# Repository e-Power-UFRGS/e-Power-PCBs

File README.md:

# e-Power-PCBs

## Index

#### e-Power_conventions: Standard conventions for all PCBs
The image shows an example with conventions regarding the description data of the PCBs. One way to implemment this conventions is oppening 2 KiCad Pcbnew windows, one with the file you want to update and other with the e-Power_conventions.kicad_pcb and the copy the standard from one window to the other (yes, this is possible on the current versions of KiCad!).

#### BMS_20S: Battery Management System with 20S measurement capability

#### TSAL: Tractive System Alternating Lights 

## License
[MIT](https://choosealicense.com/licenses/mit/)

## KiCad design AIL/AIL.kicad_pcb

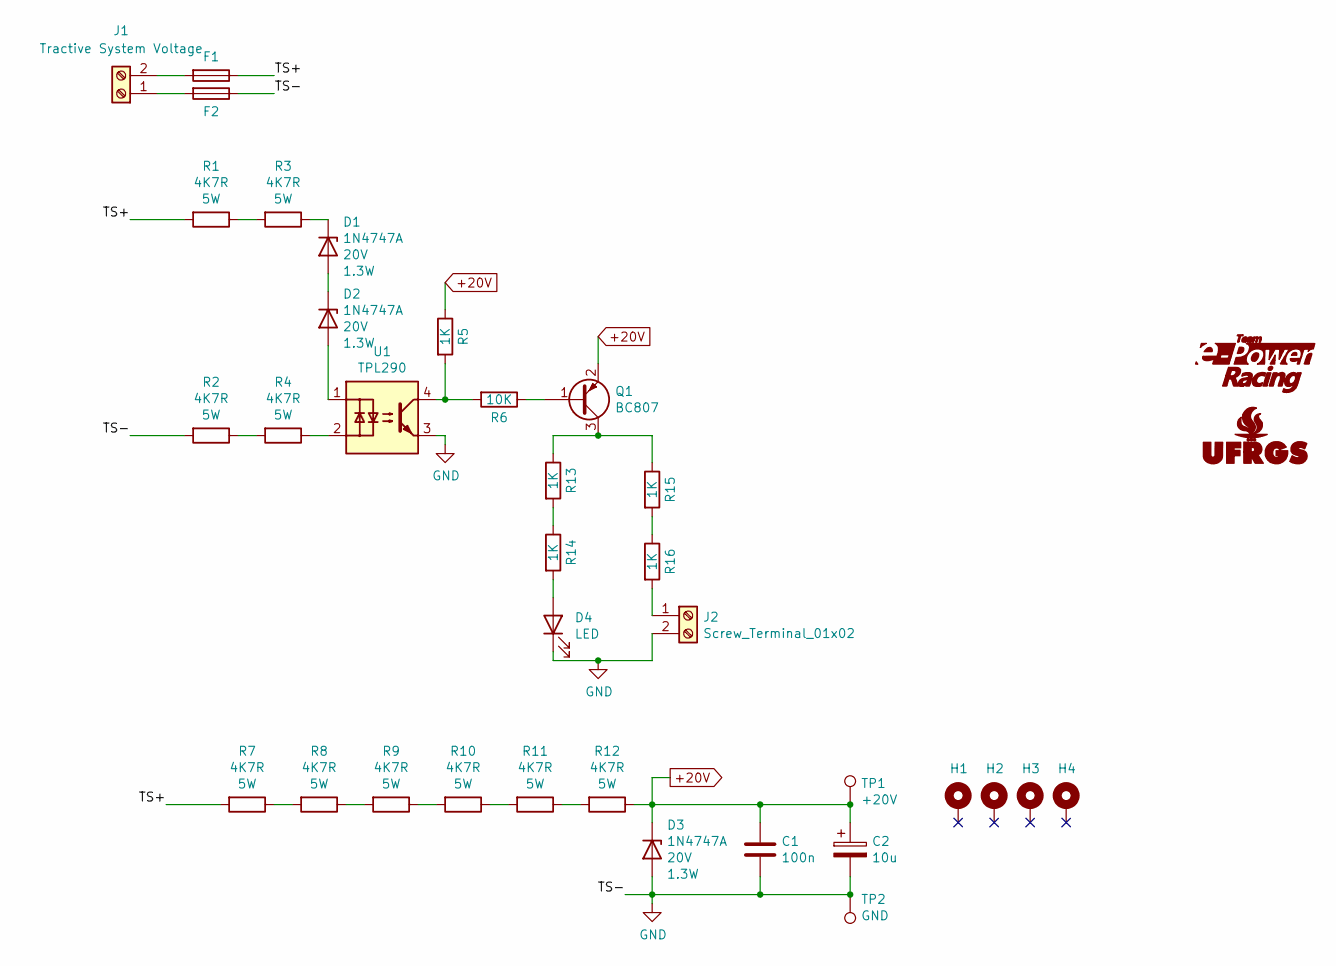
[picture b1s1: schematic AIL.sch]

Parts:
C1: 100n; C_0805_2012Metric
C2: 10u; CP_Elec_8x10
D1, D2, D3: 1N4747A; DO-35_SMD; Voltage 20V
D4: LED; LED_0805_1.15x1.40mm_HandSolder
F1, F2: Fuse_1206; FUSE_1206_3216Metric
G1: Logo_e-Power_Large; Logo_e-Power_16.5x8.0mm_SilkS
G2: Logo_UFRGS_Large; Logo_UFRGS_14.7x8.0mm_SilkS
H1, H2, H3, H4: NC; MountingHole_3.2mm_M3_Pad_Via
J1, J2: Screw_Terminal_01x02; TerminalBlock_Phoenix_MKDS-1,5-2_1x02_P5.08mm_Horizontal
Q1: BC807; SOT-23
R1, R2, R3, R4, R7, R8, R9, R10, R11, R12: 4K7R; R_Axial_DIN0617_L17.0mm_D6.0mm_P25.40mm_Horizontal
R5, R13, R14, R15, R16: 1K; R_0805_2012Metric_Pad1.15x1.40mm_HandSolder
R6: 10K; R_0805_2012Metric_Pad1.15x1.40mm_HandSolder
TP1: +20V; TestPoint_Pad_D1.0mm
TP2: GND; TestPoint_Pad_D1.0mm
U1: TPL290; DIP-4_W10.16mm

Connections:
+20V: C1.1, C2.1, D3.1 (K), Q1.2 (E), R5.1, R12.1, TP1.1
/TS+: F1.1, R1.2, R7.2
GND: C1.2, C2.2, D3.2 (A), D4.1 (K), F2.1, J2.2, R2.2, TP2.1, U1.3
unnamed: D1.1 (K), R3.1
unnamed: D1.2 (A), D2.1 (K)
unnamed: D2.2 (A), U1.1
unnamed: D4.2 (A), R14.2
unnamed: F1.2, J1.2
unnamed: F2.2, J1.1
unnamed: J2.1, R16.2
unnamed: Q1.1 (B), R6.1
unnamed: Q1.3 (C), R13.1, R15.1
unnamed: R1.1, R3.2
unnamed: R2.1, R4.2
unnamed: R4.1, U1.2
unnamed: R5.2, R6.2, U1.4
unnamed: R7.1, R8.2
unnamed: R8.1, R9.2
unnamed: R10.1, R11.2
unnamed: R9.1, R10.2
unnamed: R11.1, R12.2
unnamed: R13.2, R14.1
unnamed: R15.2, R16.1

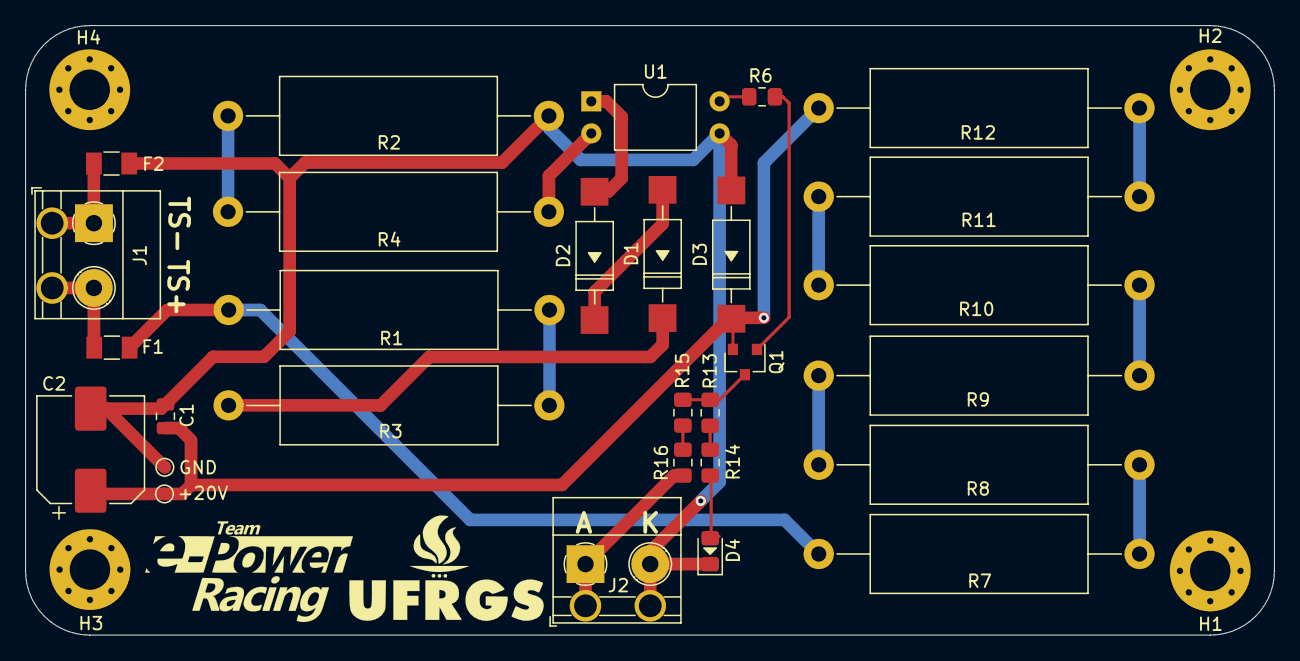
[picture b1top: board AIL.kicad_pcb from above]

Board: 2 copper layers, 98.9 x 48.3 mm, 35 parts (0 on the bottom side), 23 nets.

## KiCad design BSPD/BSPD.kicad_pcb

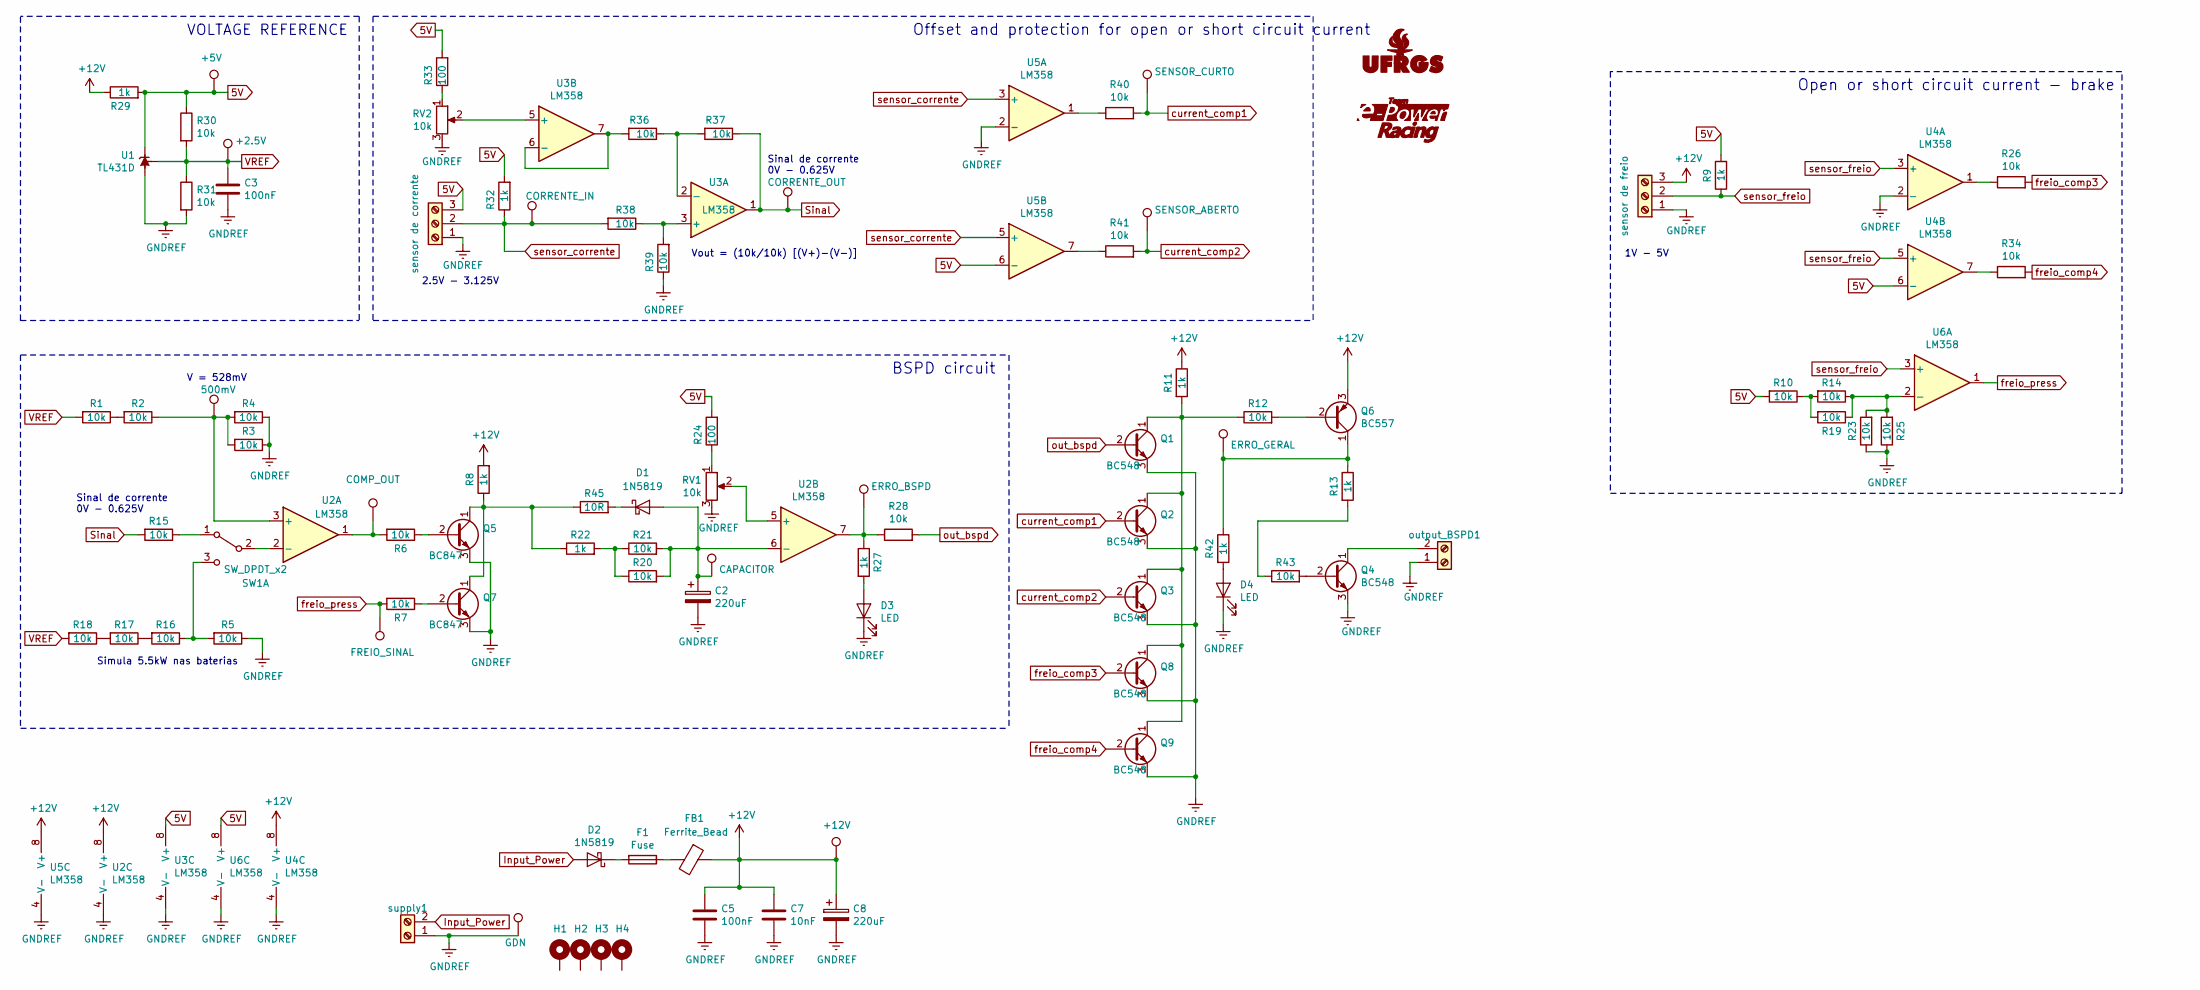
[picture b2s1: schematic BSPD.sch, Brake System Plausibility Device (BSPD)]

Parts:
C2, C8: 220uF; CP_Elec_10x10
C3, C5: 100nF; C_0805_2012Metric
C7: 10nF; C_0805_2012Metric
D1, D2: 1N5819; DO-214AC
D3, D4: LED; LED_0805_1.15x1.40mm_HandSolder
F1: Fuse; Fuse_0805_2012Metric
FB1: Ferrite_Bead; FB_0603_1608Metric
G1: Logo_UFRGS_Large; Logo_UFRGS_14.7x8.0mm_SilkS
G2: Logo_e-Power_Large; Logo_e-Power_16.5x8.0mm_SilkS
H1, H2, H3, H4: MountingHole_Pad; MountingHole_3.2mm_M3_Pad_Via
J1: sensor de corrente; TerminalBlock_Phoenix_MKDS-1,5-3_1x03_P5.00mm_Horizontal
Q1, Q2, Q3, Q4, Q8, Q9: BC548; SOT-23
Q5, Q7: BC847; SOT-23
Q6: BC557; SOT-23
R1, R2, R3, R4, R5, R6, R7, R10, R12, R14, R15, R16, R17, R18, R19, R20, R21, R23, R25, R26, R28, R30, R31, R34, R36, R37, R38, R39, R40, R41, R43: 10k; R_0805_2012Metric
R8, R9, R11, R13, R22, R27, R29, R32, R42: 1k; R_0805_2012Metric
R24, R33: 100; R_0805_2012Metric
R45: 10R; R_0805_2012Metric
RV1, RV2: 10k; Potentiometer_Bourns_3266Y_Vertical
SW1: SW_DPDT_x2; PinHeader_1x03_P2.54mm_Vertical
TP1: +5V; TestPoint_Pad_D1.0mm
TP2: 500mV; TestPoint_Pad_D1.0mm
TP3: +2.5V; TestPoint_Pad_D1.0mm
TP4: GDN; TestPoint_Pad_D1.0mm
TP5: CORRENTE_IN; TestPoint_Pad_D1.0mm
TP6: CORRENTE_OUT; TestPoint_Pad_D1.0mm
TP7: +12V; TestPoint_Pad_D1.0mm
TP8: COMP_OUT; TestPoint_Pad_D1.0mm
TP9: FREIO_SINAL; TestPoint_Pad_D1.0mm
TP10: CAPACITOR; TestPoint_Pad_D1.0mm
TP11: ERRO_BSPD; TestPoint_Pad_D1.0mm
TP12: SENSOR_CURTO; TestPoint_Pad_D1.0mm
TP13: SENSOR_ABERTO; TestPoint_Pad_D1.0mm
TP14: ERRO_GERAL; TestPoint_Pad_D1.0mm
U1: TL431D; SOT-23
U2, U3, U4, U5, U6: LM358; SOIC-8_3.9x4.9mm_P1.27mm
output_BSPD1: Screw_Terminal_01x02; TerminalBlock_Phoenix_MKDS-1,5-2_1x02_P5.08mm_Horizontal
sensor_freio1: sensor de freio; TerminalBlock_Phoenix_MKDS-1,5-3_1x03_P5.00mm_Horizontal
supply1: Screw_Terminal_01x02; TerminalBlock_Phoenix_MKDS-1,5-2_1x02_P5.08mm_Horizontal

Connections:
5V: J1.3, R9.2, R10.2, R24.2, R29.2, R30.1, R32.2, R33.2, TP1.1, U1.1 (K), U3.8 (V+), U4.6 (-), U5.6 (-), U6.8 (V+)
+12V: C5.1, C7.1, C8.1, FB1.1, Q6.3 (E), R8.2, R11.1, R29.1, TP7.1, U2.8 (V+), U4.8 (V+), U5.8 (V+), sensor_freio1.3; also elsewhere on the board
Input_Power: D2.2 (A), supply1.2; also elsewhere on the board
unnamed: C2.1, D1.2 (A), R20.2, R21.2, TP10.1, U2.6 (-)
unnamed: D1.1 (K), R45.2
unnamed: D2.1 (K), F1.2
unnamed: D3.2 (A), R27.2
unnamed: D4.2 (A), R42.2
unnamed: F1.1, FB1.2
unnamed: Q1.1 (C), Q2.1 (C), Q3.1 (C), Q8.1 (C), Q9.1 (C), R11.2, R12.1
unnamed 14: Q4.1 (C), output_BSPD1.2; also elsewhere on the board
unnamed: Q4.2 (B), R43.2
unnamed: Q5.1 (C), Q7.1 (C), R8.1, R22.1, R45.1
unnamed: Q5.2 (B), R6.1
unnamed: Q6.1 (C), R13.1, R42.1, TP14.1
unnamed: Q6.2 (B), R12.2
unnamed: Q7.2 (B), R7.1
unnamed: R1.1, R2.2
unnamed: R2.1, R3.2, R4.2, TP2.1, U2.3 (+)
unnamed: R6.2, TP8.1, U2.1
unnamed: R10.1, R14.2, R19.2
unnamed: R13.2, R43.1
unnamed: R14.1, R19.1, R23.2, R25.2, U6.2 (-)
unnamed: R15.1, SW1.1 (A)
unnamed: R5.2, R16.1, SW1.3 (C)
unnamed: R16.2, R17.1
unnamed: R17.2, R18.1
unnamed: R20.1, R21.1, R22.2
unnamed: R24.1, RV1.1
unnamed: R26.1, U4.1
unnamed: R27.1, R28.1, TP11.1, U2.7
unnamed: R33.1, RV2.1
unnamed: R34.1, U4.7
unnamed: R36.1, R37.2, U3.2 (-)
unnamed: R36.2, U3.6 (-), U3.7
unnamed: R38.1, R39.2, U3.3 (+)
unnamed: R40.1, U5.1
unnamed: R41.1, U5.7
unnamed: RV1.2, U2.5 (+)
unnamed: RV2.2, U3.5 (+)
unnamed: SW1.2 (B), U2.2 (-)
Sinal: R15.2, R37.1, TP6.1, U3.1
current_comp1: Q2.2 (B), R40.2, TP12.1
current_comp2: Q3.2 (B), R41.2, TP13.1
freio_comp3: Q8.2 (B), R26.2
freio_comp4: Q9.2 (B), R34.2
freio_press: R7.2, TP9.1, U6.1
out_bspd: Q1.2 (B), R28.2
sensor_corrente: J1.2, R32.1, R38.2, TP5.1, U5.3 (+), U5.5 (+)
sensor_freio: R9.1, U4.3 (+), U4.5 (+), U6.3 (+), sensor_freio1.2; also elsewhere on the board

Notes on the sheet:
VOLTAGE REFERENCE
Offset and protection for open or short circuit current
BSPD circuit
Vout = (10k/10k) [(V+)-(V-)]
Simula 5.5kW nas baterias
V = 528mV
2.5V - 3.125V
Sinal de corrente 0V - 0.625V
1V - 5V
Open or short circuit current - brake

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
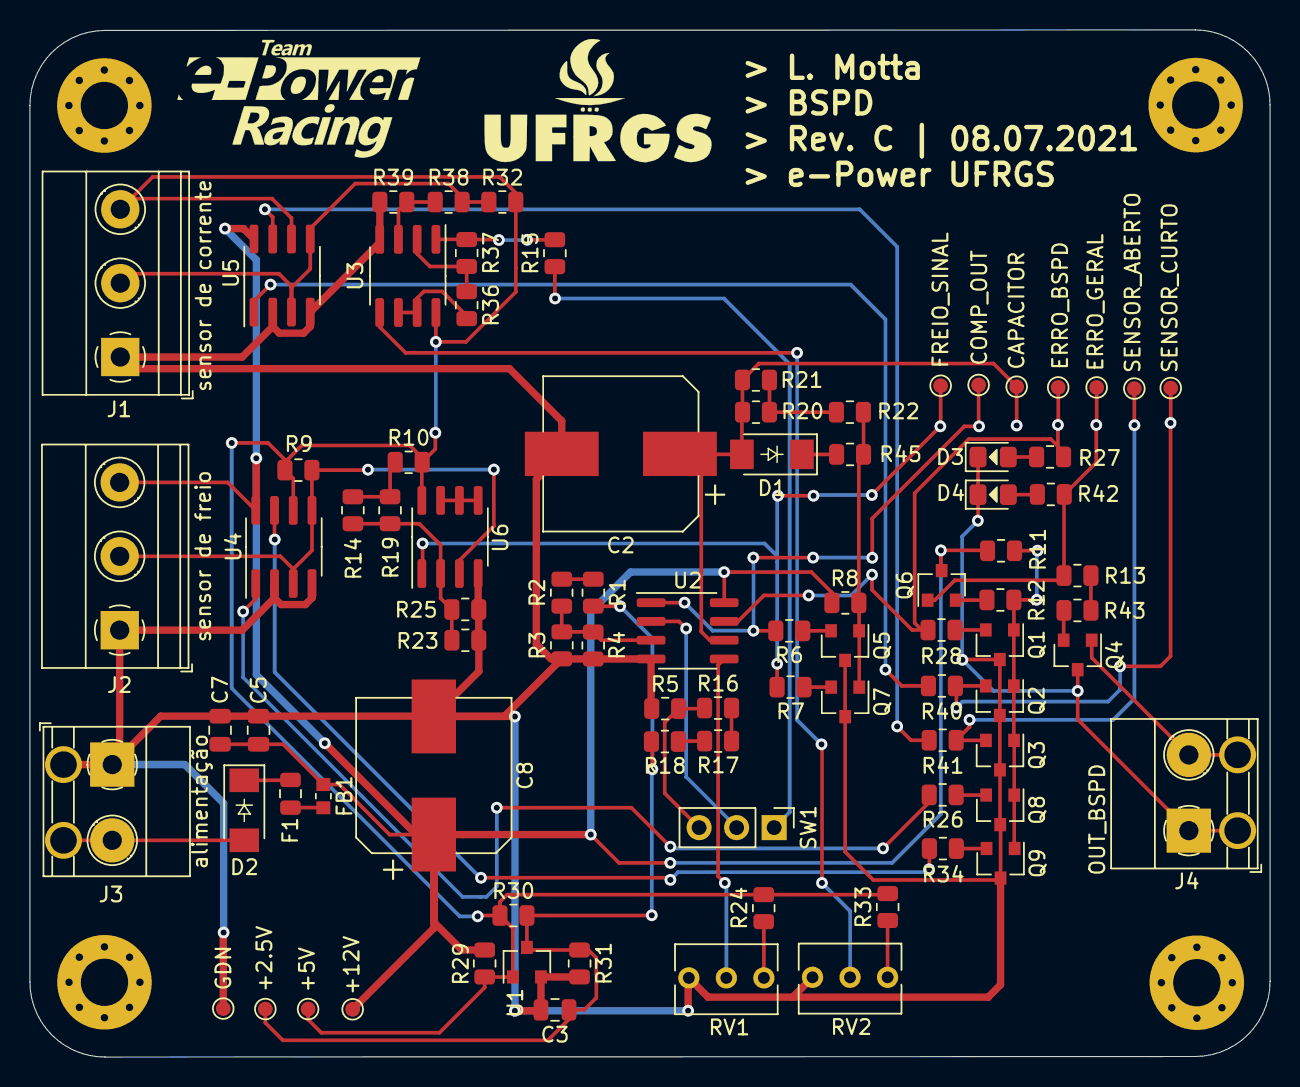
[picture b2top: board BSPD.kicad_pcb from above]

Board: 2 copper layers, 84.0 x 69.5 mm, 93 parts (0 on the bottom side), 52 nets.

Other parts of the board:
J2: sensor de freio; TerminalBlock_Phoenix_MKDS-1,5-3_1x03_P5.00mm_Horizontal
J3: alimentação; TerminalBlock_Phoenix_MKDS-1,5-2_1x02_P5.08mm_Horizontal
J4: OUT_BSPD; TerminalBlock_Phoenix_MKDS-1,5-2_1x02_P5.08mm_Horizontal

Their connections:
+12V: J2.3; also elsewhere on the board
Input_Power: J3.2; also elsewhere on the board
unnamed 14: J4.2; also elsewhere on the board
sensor_freio: J2.2; also elsewhere on the board

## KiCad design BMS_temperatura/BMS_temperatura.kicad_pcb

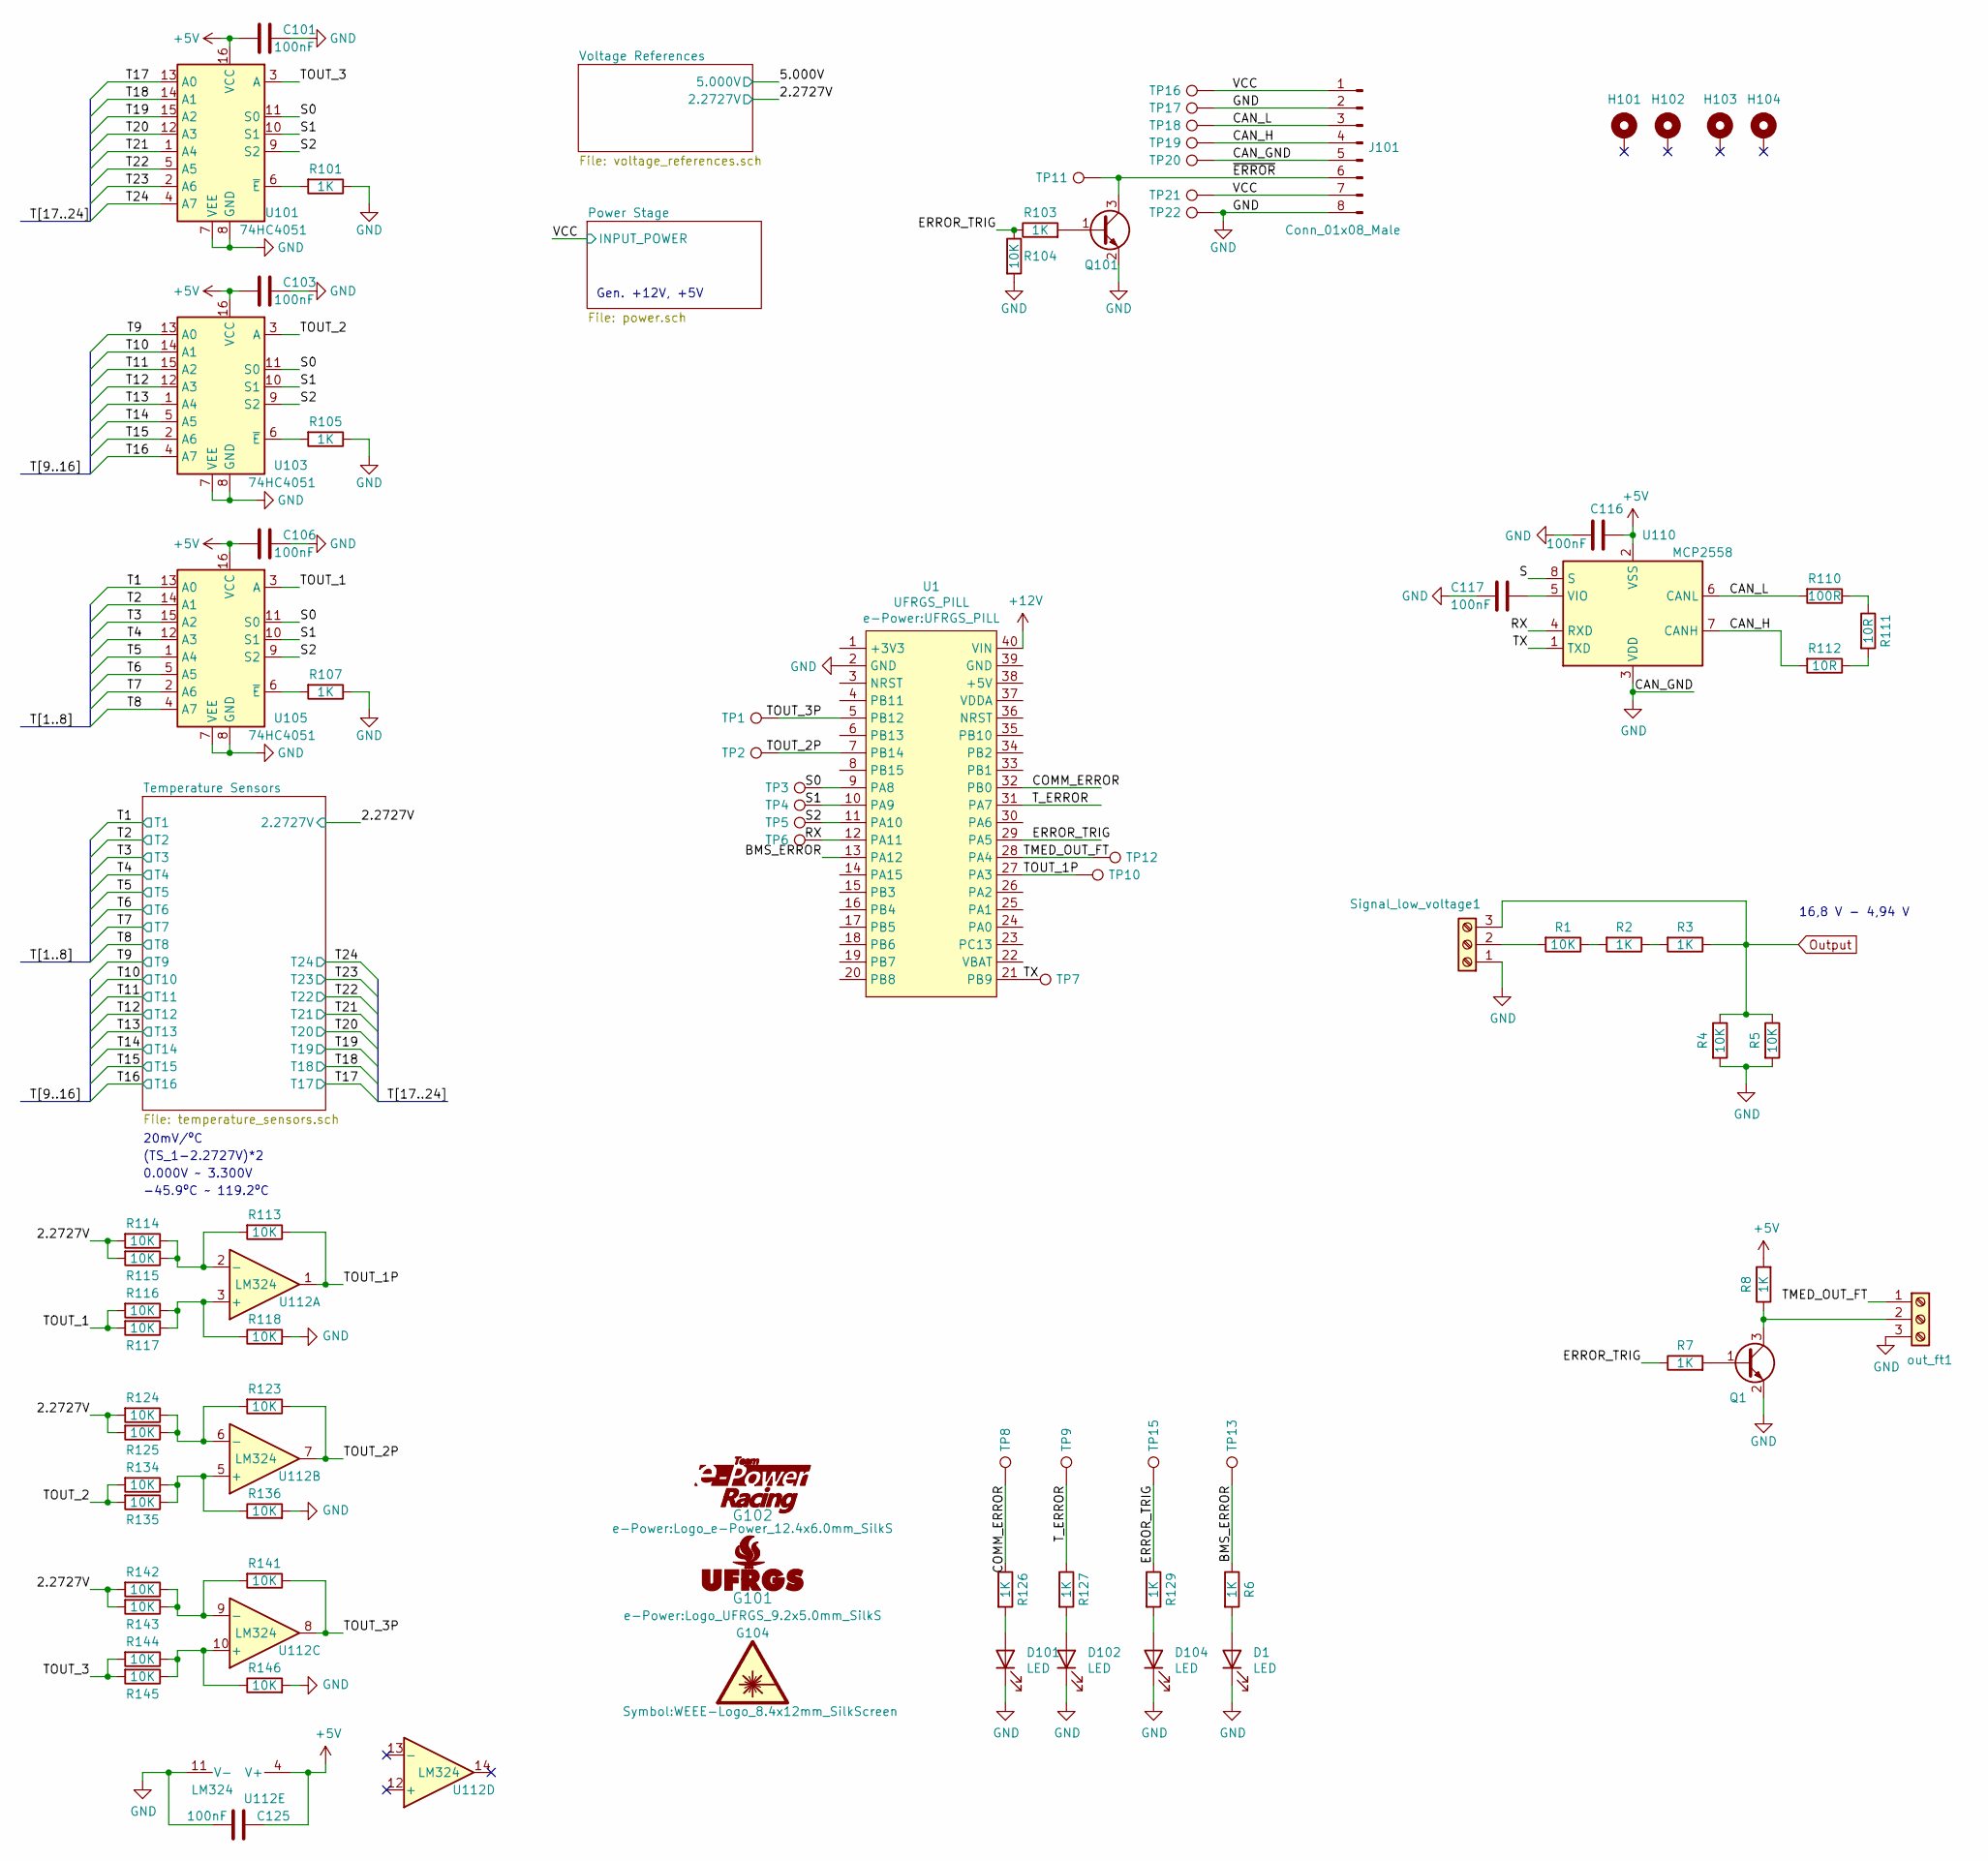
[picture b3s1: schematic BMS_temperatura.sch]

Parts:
C101, C103, C106, C116, C117, C125: 100nF; C_0805_2012Metric; Voltage 50V; LCSC C49678
D1, D101, D102, D104: LED; LED_0805_1.15x1.40mm_HandSolder
G101: Logo_UFRGS_Large; Logo_UFRGS_9.2x5.0mm_SilkS
G102: Logo_e-Power_Large; Logo_e-Power_12.4x6.0mm_SilkS
G104: SYM_LASER_Large; WEEE-Logo_8.4x12mm_SilkScreen
H101, H102, H103, H104: GND; MountingHole_3.2mm_M3_Pad_Via
J101: Conn_01x08_Male; Molex_Mini-Fit_Jr_2x04_P4.20mm_Horizontal
Q1, Q101: MMBT3904; SOT-23; LCSC C20526
R1, R4, R5: 10K; R_0805_2012Metric; Voltage 150V; LCSC C17513
R2, R3, R6, R7, R8, R101, R103, R105, R107, R126, R127, R129: 1K; R_0805_2012Metric; Voltage 150V; LCSC C17513
R104, R113, R114, R115, R116, R117, R118, R123, R124, R125, R134, R135, R136, R141, R142, R143, R144, R145, R146: 10K; R_0805_2012Metric; Voltage 150V; LCSC C17414
R110: 100R; R_0805_2012Metric; Voltage 150V; LCSC C17408
R111, R112: 10R; R_0805_2012Metric; Voltage 150V; LCSC C17415
Signal_low_voltage1: Screw_Terminal_01x03; TerminalBlock_Phoenix_MKDS-1,5-3_1x03_P5.00mm_Horizontal
TP1: TOUT_3P; TestPoint_Pad_D1.0mm
TP2: TOUT_2P; TestPoint_Pad_D1.0mm
TP3: S0; TestPoint_Pad_D1.0mm
TP4: S1; TestPoint_Pad_D1.0mm
TP5: S2; TestPoint_Pad_D1.0mm
TP6: RX; TestPoint_Pad_D1.0mm
TP7: TX; TestPoint_Pad_D1.0mm
TP8: C_ERROR; TestPoint_Pad_D1.0mm
TP9: T_ERROR; TestPoint_Pad_D1.0mm
TP10: TOUT_1P; TestPoint_Pad_D1.0mm
TP11: ~ERROR; TestPoint_Pad_D1.0mm
TP12: TMED_OUT_FT; TestPoint_Pad_D1.0mm
TP13: BMS_ERROR; TestPoint_Pad_D1.0mm
TP15: ERROR_TRIG; TestPoint_Pad_D1.0mm
TP16, TP21: VCC; TestPoint_Pad_D1.0mm
TP17: GND; TestPoint_Pad_D1.0mm
TP18: CAN_L; TestPoint_Pad_D1.0mm
TP19: CAN_H; TestPoint_Pad_D1.0mm
TP20: CAN_GND; TestPoint_Pad_D1.0mm
TP22: GNG; TestPoint_Pad_D1.0mm
U1: UFRGS_PILL
U101, U103, U105: 74HC4051; SOP-16_4.4x10.4mm_P1.27mm; LCSC C9386
U110: MCP2558; SOIC-8_3.9x4.9mm_P1.27mm
U112: LM324; SOIC-14_3.9x8.7mm_P1.27mm; LCSC C71035
out_ft1: Screw_Terminal_01x03; TerminalBlock_Phoenix_MKDS-1,5-3_1x03_P5.00mm_Horizontal

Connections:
+5V: C101.2, C103.2, C106.2, C116.1, C125.1, R8.2, U101.16 (VCC), U103.16 (VCC), U105.16 (VCC), U110.2 (VSS), U112.4 (V+); also elsewhere on the board
+12V: U1.40 (VIN); also elsewhere on the board
/2.2727V: R114.2, R115.2, R124.2, R125.2, R142.2, R143.2; also elsewhere on the board
/BMS_ERROR: R6.1, TP13.1, U1.13 (PA12)
/CAN_H: J101.4, R112.2, TP19.1, U110.7 (CANH)
/CAN_L: J101.3, R110.2, TP18.1, U110.6 (CANL)
/COMM_ERROR: R126.1, TP8.1, U1.32 (PB0)
/ERROR_TRIG: R7.1, R103.1, R104.1, R129.1, TP15.1, U1.29 (PA5)
/RX: TP6.1, U1.12 (PA11), U110.4 (RXD)
/S: U110.8 (S)
/S0: TP3.1, U1.9 (PA8), U101.11 (S0), U103.11 (S0), U105.11 (S0)
/S1: TP4.1, U1.10 (PA9), U101.10 (S1), U103.10 (S1), U105.10 (S1)
/S2: TP5.1, U1.11 (PA10), U101.9 (S2), U103.9 (S2), U105.9 (S2)
/T1: U105.13 (A0); also elsewhere on the board
/T2: U105.14 (A1); also elsewhere on the board
/T3: U105.15 (A2); also elsewhere on the board
/T4: U105.12 (A3); also elsewhere on the board
/T5: U105.1 (A4); also elsewhere on the board
/T6: U105.5 (A5); also elsewhere on the board
/T7: U105.2 (A6); also elsewhere on the board
/T8: U105.4 (A7); also elsewhere on the board
/T9: U103.13 (A0); also elsewhere on the board
/T10: U103.14 (A1); also elsewhere on the board
/T11: U103.15 (A2); also elsewhere on the board
/T12: U103.12 (A3); also elsewhere on the board
/T13: U103.1 (A4); also elsewhere on the board
/T14: U103.5 (A5); also elsewhere on the board
/T15: U103.2 (A6); also elsewhere on the board
/T16: U103.4 (A7); also elsewhere on the board
/T17: U101.13 (A0); also elsewhere on the board
/T18: U101.14 (A1); also elsewhere on the board
/T19: U101.15 (A2); also elsewhere on the board
/T20: U101.12 (A3); also elsewhere on the board
/T21: U101.1 (A4); also elsewhere on the board
/T22: U101.5 (A5); also elsewhere on the board
/T23: U101.2 (A6); also elsewhere on the board
/T24: U101.4 (A7); also elsewhere on the board
/TMED_OUT_FT: TP12.1, U1.28 (PA4), out_ft1.1
/TOUT_1: R116.2, R117.2, U105.3 (A)
/TOUT_1P: R113.1, TP10.1, U1.27 (PA3), U112.1
/TOUT_2: R134.2, R135.2, U103.3 (A)
/TOUT_2P: R123.1, TP2.1, U1.7 (PB14), U112.7
/TOUT_3: R144.2, R145.2, U101.3 (A)
/TOUT_3P: R141.1, TP1.1, U1.5 (PB12), U112.8
/TX: TP7.1, U1.21 (PB9), U110.1 (TXD)
/T_ERROR: R127.1, TP9.1, U1.31 (PA7)
/VCC: J101.1, J101.7, TP16.1, TP21.1; also elsewhere on the board
/~ERROR: J101.6, Q101.3 (C), TP11.1
GND: C101.1, C103.1, C106.1, C116.2, C117.2, C125.2, D1.1 (K), D101.1 (K), D102.1 (K), D104.1 (K), J101.2, J101.5, J101.8, Q1.2 (E), Q101.2 (E), R4.2, R5.2, R101.1, R104.2, R105.1, R107.1, R118.2, R136.2, R146.2, Signal_low_voltage1.1, TP17.1, TP20.1, TP22.1, U1.2 (GND), U101.7 (VEE), U101.8 (GND), U103.7 (VEE), U103.8 (GND), U105.7 (VEE), U105.8 (GND), U110.3 (VDD), U112.11 (V-), out_ft1.3; also elsewhere on the board
unnamed: C117.1, U110.5 (VIO)
unnamed: D1.2 (A), R6.2
unnamed: D101.2 (A), R126.2
unnamed: D102.2 (A), R127.2
unnamed: D104.2 (A), R129.2
unnamed: Q1.1 (B), R7.2
unnamed: Q1.3 (C), R8.1, out_ft1.2
unnamed: Q101.1 (B), R103.2
unnamed: R1.1, R2.2
unnamed: R1.2, Signal_low_voltage1.2
unnamed: R2.1, R3.2
unnamed: R101.2, U101.6 (~E)
unnamed: R105.2, U103.6 (~E)
unnamed: R107.2, U105.6 (~E)
unnamed: R110.1, R111.1
unnamed: R111.2, R112.1
unnamed: R113.2, R114.1, R115.1, U112.2 (-)
unnamed: R116.1, R117.1, R118.1, U112.3 (+)
unnamed: R123.2, R124.1, R125.1, U112.6 (-)
unnamed: R134.1, R135.1, R136.1, U112.5 (+)
unnamed: R141.2, R142.1, R143.1, U112.9 (-)
unnamed: R144.1, R145.1, R146.1, U112.10 (+)
Output: R3.1, R4.1, R5.1, Signal_low_voltage1.3

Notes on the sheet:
Gen. +12V, +5V
-45.9ºC ~~ 119.2ºC
0.000V ~~ 3.300V
(TS_1-2.2727V)*2
20mV/ºC
16,8 V - 4,94 V

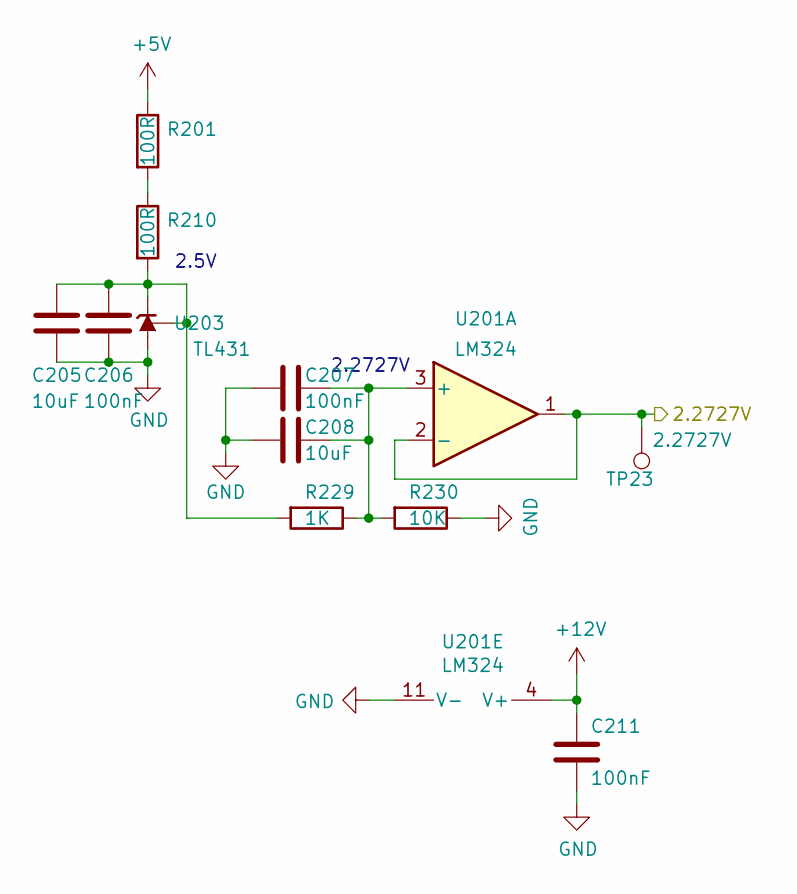
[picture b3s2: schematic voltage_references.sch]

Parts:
C205, C208: 10uF; C_0805_2012Metric; LCSC C15850
C206, C207, C211: 100nF; C_0805_2012Metric; Voltage 50V; LCSC C49678
R201, R210: 100R; R_0805_2012Metric; LCSC C17408
R229: 1K; R_0805_2012Metric; Voltage 150V; LCSC C17513
R230: 10K; R_0805_2012Metric; Voltage 150V; LCSC C17414
TP23: 2.2727V; TestPoint_Pad_D1.0mm
U201: LM324; SOIC-14_3.9x8.7mm_P1.27mm; LCSC C71035
U203: TL431; SOT-23; LCSC C3113

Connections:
+5V: R201.1; also elsewhere on the board
+12V: C211.1, U201.4 (V+); also elsewhere on the board
/2.2727V: TP23.1, U201.1, U201.2 (-); also elsewhere on the board
GND: C205.2, C206.2, C207.2, C208.2, C211.2, R230.1, U201.11 (V-), U203.3 (A); also elsewhere on the board
unnamed: C205.1, C206.1, R210.2, R229.2, U203.1 (REF), U203.2 (K)
unnamed: C207.1, C208.1, R229.1, R230.2, U201.3 (+)
unnamed: R201.2, R210.1

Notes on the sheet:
2.5V
2.2727V

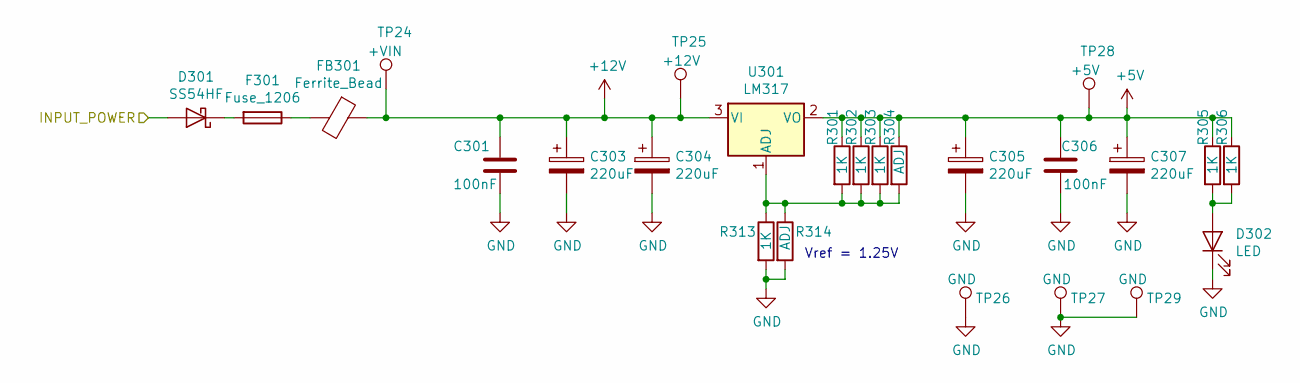
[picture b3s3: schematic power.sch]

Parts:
C301, C306: 100nF; C_0805_2012Metric; Voltage 50V; LCSC C49678
C303, C304, C305, C307: 220uF; CP_Elec_10x10
D301: SS54HF; DO-214AC
D302: LED; LED_0805_1.15x1.40mm_HandSolder
F301: Fuse_1206; FUSE_1206_3216Metric
FB301: Ferrite_Bead; FB_0805_2012Metric; LCSC C1017
R301, R302, R303, R305, R306, R313: 1K; R_0805_2012Metric; Voltage 150V; LCSC C17513
R304, R314: ADJ; R_0805_2012Metric
TP24: +VIN; TestPoint_Pad_D1.0mm
TP25: +12V; TestPoint_Pad_D1.0mm
TP26, TP27, TP29: GND; TestPoint_Pad_D1.0mm
TP28: +5V; TestPoint_Pad_D1.0mm
U301: LM317; TO-220-3_Horizontal_TabDown

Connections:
+5V: C305.1, C306.1, C307.1, R301.1, R302.1, R303.1, R304.1, R305.1, R306.1, TP28.1, U301.2 (VO); also elsewhere on the board
+12V: C301.1, C303.1, C304.1, FB301.1, TP24.1, TP25.1, U301.3 (VI); also elsewhere on the board
/VCC: D301.2 (A); also elsewhere on the board
GND: C301.2, C303.2, C304.2, C305.2, C306.2, C307.2, D302.1 (K), R313.2, R314.2, TP26.1, TP27.1, TP29.1; also elsewhere on the board
unnamed: D301.1 (K), F301.2
unnamed: D302.2 (A), R305.2, R306.2
unnamed: F301.1, FB301.2
unnamed: R301.2, R302.2, R303.2, R304.2, R313.1, R314.1, U301.1 (ADJ)

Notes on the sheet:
Vref = 1.25V

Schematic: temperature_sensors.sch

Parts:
J1: TEMP_IDC_26_CONN; IDC-Header_2x13_P2.54mm_Horizontal

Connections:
/Temperature Sensors/TS_1: J1.25; also elsewhere on the board
/Temperature Sensors/TS_2: J1.26; also elsewhere on the board
/Temperature Sensors/TS_3: J1.15; also elsewhere on the board
/Temperature Sensors/TS_4: J1.16; also elsewhere on the board
/Temperature Sensors/TS_5: J1.23; also elsewhere on the board
/Temperature Sensors/TS_6: J1.24; also elsewhere on the board
/Temperature Sensors/TS_7: J1.17; also elsewhere on the board
/Temperature Sensors/TS_8: J1.18; also elsewhere on the board
/Temperature Sensors/TS_9: J1.21; also elsewhere on the board
/Temperature Sensors/TS_10: J1.22; also elsewhere on the board
/Temperature Sensors/TS_11: J1.19; also elsewhere on the board
/Temperature Sensors/TS_12: J1.20; also elsewhere on the board
/Temperature Sensors/TS_13: J1.14; also elsewhere on the board
/Temperature Sensors/TS_14: J1.13; also elsewhere on the board
/Temperature Sensors/TS_15: J1.3; also elsewhere on the board
/Temperature Sensors/TS_16: J1.4; also elsewhere on the board
/Temperature Sensors/TS_17: J1.12; also elsewhere on the board
/Temperature Sensors/TS_18: J1.11; also elsewhere on the board
/Temperature Sensors/TS_19: J1.5; also elsewhere on the board
/Temperature Sensors/TS_20: J1.6; also elsewhere on the board
/Temperature Sensors/TS_21: J1.10; also elsewhere on the board
/Temperature Sensors/TS_22: J1.9; also elsewhere on the board
/Temperature Sensors/TS_23: J1.7; also elsewhere on the board
/Temperature Sensors/TS_24: J1.8; also elsewhere on the board
GND: J1.1, J1.2; also elsewhere on the board
